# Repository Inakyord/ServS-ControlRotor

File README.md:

# ServS-ControlRotor
Making a system to control de rotors of an antenna pointing system

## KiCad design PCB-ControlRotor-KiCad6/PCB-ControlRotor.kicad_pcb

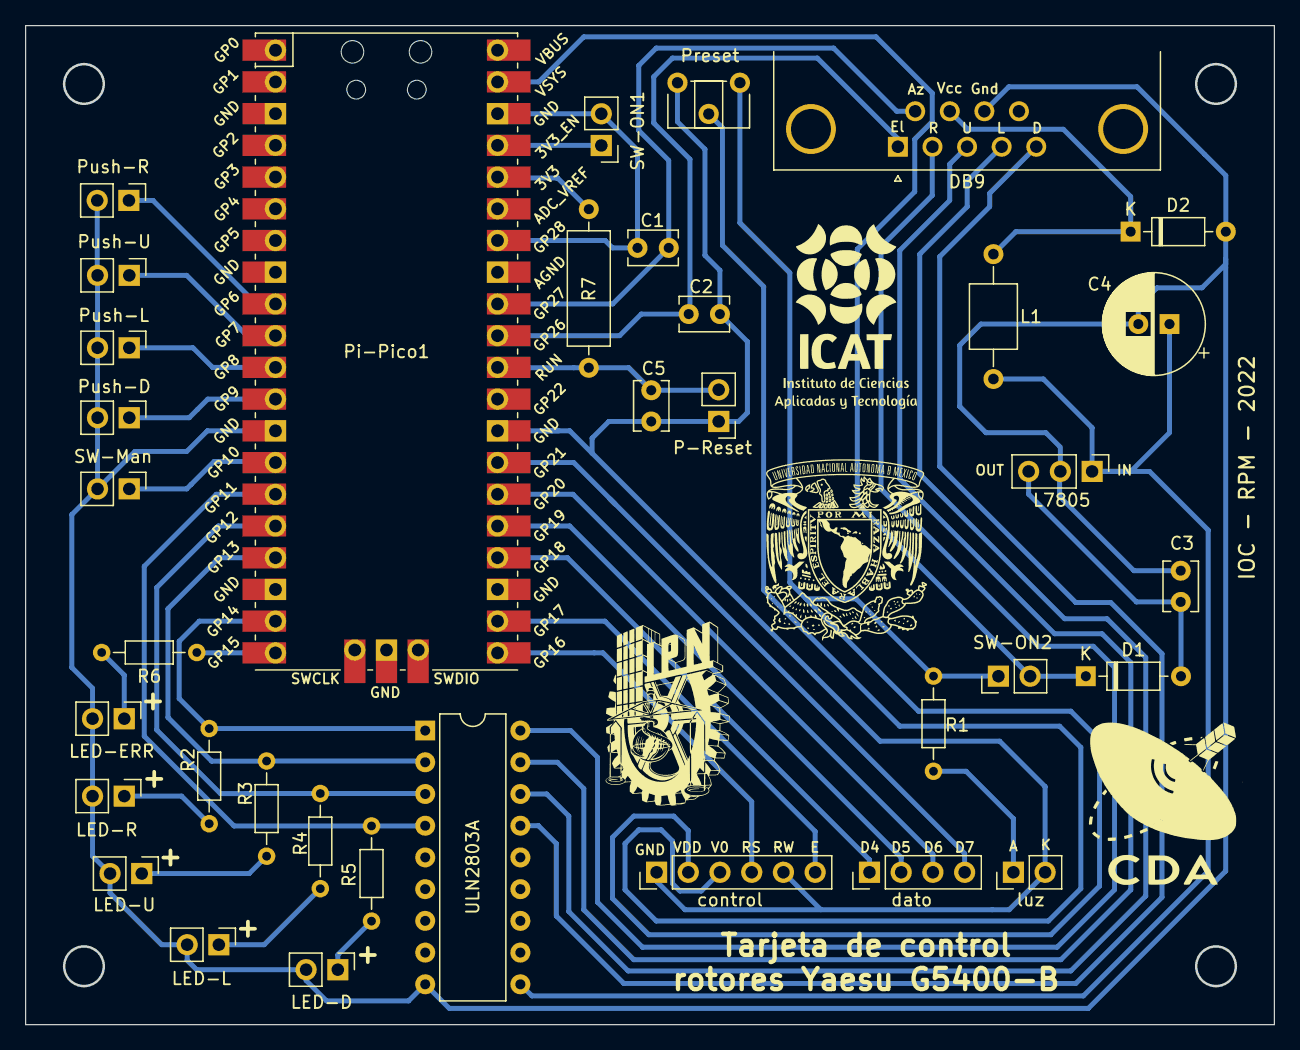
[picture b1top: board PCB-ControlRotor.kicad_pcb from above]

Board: 2 copper layers, 100.0 x 80.0 mm, 36 parts (0 on the bottom side), 40 nets.

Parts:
C1, C2, C3: 100n; C_Disc_D3.8mm_W2.6mm_P2.50mm
C4: 100u; CP_Radial_D8.0mm_P2.50mm
C5: 10n; C_Disc_D3.8mm_W2.6mm_P2.50mm
D1, D2: 1N4148; D_DO-35_SOD27_P7.62mm_Horizontal
DB9: DB9_Female_MountingHoles; DSUB-9_Female_Horizontal_P2.77x2.84mm_EdgePinOffset7.70mm_H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
L1: L_Ferrite; L_Axial_L5.0mm_D3.6mm_P10.00mm_Horizontal_Murata_BL01RN1A2A2
L7805: L7805; PinHeader_1x03_P2.54mm_Vertical
LED-D: Conn_01x02_Male; PinHeader_1x02_P2.54mm_Vertical
LED-ERR: Conn_01x02_Male; PinHeader_1x02_P2.54mm_Vertical
LED-L: Conn_01x02_Male; PinHeader_1x02_P2.54mm_Vertical
LED-R: Conn_01x02_Male; PinHeader_1x02_P2.54mm_Vertical
LED-U: Conn_01x02_Male; PinHeader_1x02_P2.54mm_Vertical
P-Reset: Conn_01x02_Male; PinHeader_1x02_P2.54mm_Vertical
Pi-Pico1: Pico; RPi_Pico_SMD_TH
Preset: 10k; Potentiometer_ACP_CA6-H2,5_Horizontal
Push-D: Conn_01x02_Male; PinHeader_1x02_P2.54mm_Vertical
Push-L: Conn_01x02_Male; PinHeader_1x02_P2.54mm_Vertical
Push-R: Conn_01x02_Male; PinHeader_1x02_P2.54mm_Vertical
Push-U: Conn_01x02_Male; PinHeader_1x02_P2.54mm_Vertical
R1, R2, R3, R4, R5, R6: 220; R_Axial_DIN0204_L3.6mm_D1.6mm_P7.62mm_Horizontal
R7: 10k; R_Axial_DIN0309_L9.0mm_D3.2mm_P12.70mm_Horizontal
SW-Man: Conn_01x02_Male; PinHeader_1x02_P2.54mm_Vertical
SW-ON1, SW-ON2: Conn_01x02_Male; PinHeader_1x02_P2.54mm_Vertical
ULN2803A: ULN2803A; DIP-18_W7.62mm
control: Conn_01x06_Male; PinHeader_1x06_P2.54mm_Vertical
dato: Conn_01x08_Male; PinHeader_1x04_P2.54mm_Vertical
luz: Conn_01x02_Male; PinHeader_1x02_P2.54mm_Vertical

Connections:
+15V: C4.1, L1.2, L7805.1 (IN), ULN2803A.10 (COM)
/AZ: C1.1, DB9.6, Pi-Pico1.32 (GPIO27_ADC1)
/D: DB9.5, ULN2803A.15 (O4)
/EL: C2.1, DB9.1, Pi-Pico1.31 (GPIO26_ADC0)
/L: DB9.4, ULN2803A.16 (O3)
/R: DB9.2, ULN2803A.18 (O1)
/U: DB9.3, ULN2803A.17 (O2)
GND: C3.1, C4.2, D2.2 (A), DB9.8, L7805.2 (GND), LED-D.2, LED-ERR.2, LED-L.2, LED-R.2, LED-U.2, Pi-Pico1.13 (GND), Push-D.2, Push-L.2, Push-R.2, Push-U.2, SW-Man.2, ULN2803A.9 (GND)
unnamed: R1.2, luz.1
unnamed: C2.2, C5.2, P-Reset.1, Pi-Pico1.28 (GND), Preset.3, control.1, control.5, luz.2
unnamed: C1.2, Pi-Pico1.34 (GPIO28_ADC2), Pi-Pico1.38 (GND), SW-ON1.2
unnamed: C3.2, D1.2 (A), L7805.3 (OUT)
unnamed: C5.1, P-Reset.2, Pi-Pico1.30 (RUN), R7.1
unnamed: Preset.1, R1.1, SW-ON2.1, control.2
unnamed: Preset.2, control.3
unnamed: Pi-Pico1.21 (GPIO16), control.4
unnamed: Pi-Pico1.22 (GPIO17), control.6
unnamed: D1.1 (K), Pi-Pico1.39 (VSYS), SW-ON2.2
unnamed: D2.1 (K), DB9.7, L1.1
unnamed: LED-R.1, R2.1
unnamed: LED-ERR.1, R6.1
unnamed: LED-U.1, R3.1
unnamed: LED-D.1, R5.1
unnamed: LED-L.1, R4.1
unnamed: Pi-Pico1.24 (GPIO18), dato.1
unnamed: Pi-Pico1.25 (GPIO19), dato.2
unnamed: Pi-Pico1.26 (GPIO20), dato.3
unnamed: Pi-Pico1.27 (GPIO21), dato.4
unnamed: Pi-Pico1.9 (GPIO6), Push-R.1
unnamed: Pi-Pico1.10 (GPIO7), Push-U.1
unnamed: Pi-Pico1.11 (GPIO8), Push-L.1
unnamed: Pi-Pico1.12 (GPIO9), Push-D.1
unnamed: Pi-Pico1.14 (GPIO10), SW-Man.1
unnamed: Pi-Pico1.15 (GPIO11), R5.2, ULN2803A.4 (I4)
unnamed: Pi-Pico1.16 (GPIO12), R4.2, ULN2803A.3 (I3)
unnamed: Pi-Pico1.17 (GPIO13), R3.2, ULN2803A.2 (I2)
unnamed: Pi-Pico1.19 (GPIO14), R2.2, ULN2803A.1 (I1)
unnamed: Pi-Pico1.20 (GPIO15), R6.2
unnamed: Pi-Pico1.36 (3V3), R7.2
unnamed: Pi-Pico1.37 (3V3_EN), SW-ON1.1
